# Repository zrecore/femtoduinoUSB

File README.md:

femtoduinoUSB
=============

Latest revision: FemtoduinoUSB r14.2

See the FemtoduinoUSB_r14 folder. It is a 4-layer EAGLE PCB design + schematic.

FemtoduinoUSB ATMEGA328P-MU Arduino Clone. Originally based on the Femtoduino by Fabio Varesano. Modified by Alex Albino to include FTDI USB to serial integration.

The femtoduino, and femtoduinoUSB is released under the following license: 

   CC-BY-SA 3.0 Unported
   http://creativecommons.org/licenses/by-sa/3.0/

The USB to UART circuit was completed in part thanks to Jim Paris' super-awesome MicroFTX schematics (http://jim.sh/ftx/), which are released under the following license:

   Creative Commons Attribution-ShareAlike 3.0 Unported License
   http://creativecommons.org/licenses/by-sa/3.0/
The pins on the latest revision are corrected to align perfectly with the original Femtoduino pin positions.

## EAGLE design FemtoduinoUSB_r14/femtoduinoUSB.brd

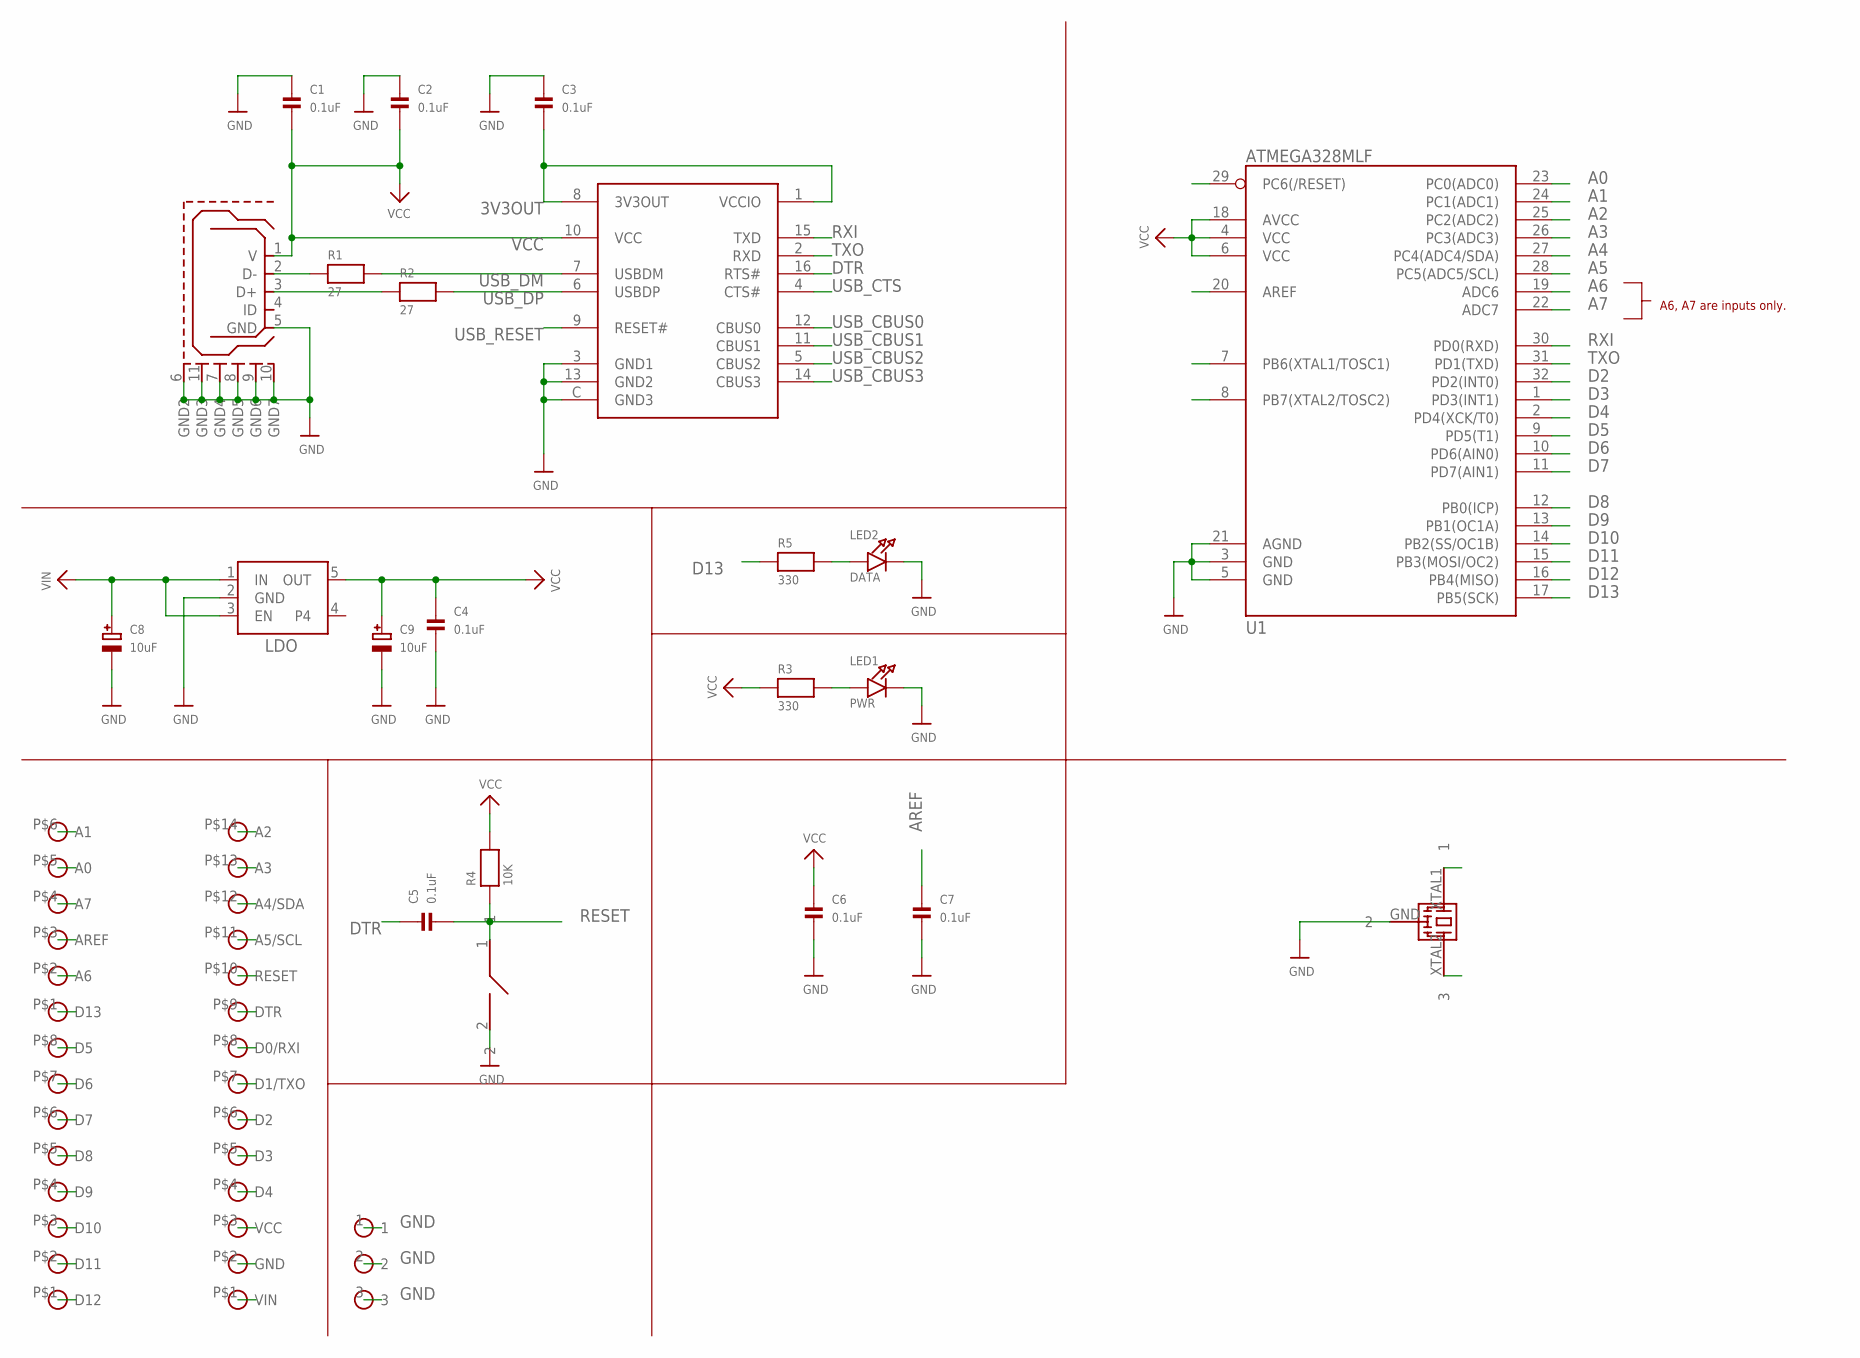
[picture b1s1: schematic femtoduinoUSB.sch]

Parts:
C1, C2, C3, C4, C5, C6, C7: 0.1uF; _0402MP
C8, C9: 10uF; EIA3216-18/A-R
LED1: PWR; CHIPLED_0603_NOOUTLINE
LED2: DATA; CHIPLED_0603_NOOUTLINE
R1, R2: 27; _0402MP
R3, R5: 330; _0402MP
R4: 10K; _0402
U1: ATMEGA328MLF; MLF32
U$1: FT230XQ
U$2: 05_PINHEAD_1X6; 05_PINHEAD_1X6_PACKAGE
U$3: 05_PINHEAD_1X8; 05_PINHEAD_1X8_PACKAGE
U$4: 05_PINHEAD_1X14; 05_PINHEAD_1X14_PACKAGE
U$6: USB_MICROB; USB_MICROB_PACKAGE
U$10: LDO_REGULATOR
U$17: SPST_SMD
U$22: CSTCE16MOV51-RO; CSTCE16M0V51-RO_PACKAGE
U$28: 05_PINHEAD_HEADER_1X3; 05_PINHEAD_1X3_HEAD_PACKAGE

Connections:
3V3OUT: C3.2, U$1.1 (VCCIO), U$1.8 (3V3OUT)
A0: U1.23 (PC0(ADC0)), U$2.P$5 (A0)
A1: U1.24 (PC1(ADC1)), U$2.P$6 (A1)
A2: U1.25 (PC2(ADC2)), U$4.P$14 (A2)
A3: U1.26 (PC3(ADC3)), U$4.P$13 (A3)
A4: U1.27 (PC4(ADC4/SDA)), U$4.P$12 (A4/SDA)
A5: U1.28 (PC5(ADC5/SCL)), U$4.P$11 (A5/SCL)
A6: U1.19 (ADC6), U$2.P$2 (A6)
A7: U1.22 (ADC7), U$2.P$4 (A7)
AREF: C7.1, U1.20 (AREF), U$2.P$3 (AREF)
D2: U1.32 (PD2(INT0)), U$4.P$6 (D2)
D3: U1.1 (PD3(INT1)), U$4.P$5 (D3)
D4: U1.2 (PD4(XCK/T0)), U$4.P$4 (D4)
D5: U1.9 (PD5(T1)), U$3.P$8 (D5)
D6: U1.10 (PD6(AIN0)), U$3.P$7 (D6)
D7: U1.11 (PD7(AIN1)), U$3.P$6 (D7)
D8: U1.12 (PB0(ICP)), U$3.P$5 (D8)
D9: U1.13 (PB1(OC1A)), U$3.P$4 (D9)
D10: U1.14 (PB2(SS/OC1B)), U$3.P$3 (D10)
D11: U1.15 (PB3(MOSI/OC2)), U$3.P$2 (D11)
D12: U1.16 (PB4(MISO)), U$3.P$1 (D12)
D13: R5.1, U1.17 (PB5(SCK)), U$2.P$1 (D13)
DTR: C5.1, U$1.16 (RTS#), U$4.P$9 (DTR)
GND: C1.1, C2.1, C3.1, C4.2, C6.2, C7.2, C8.-, C9.-, LED1.C, LED2.C, U1.3 (GND), U1.5 (GND), U1.21 (AGND), U$1.3 (GND1), U$1.13 (GND2), U$1.C (GND3), U$4.P$2 (GND), U$6.5 (GND), U$6.6 (GND2), U$6.7 (GND4), U$6.8 (GND5), U$6.9 (GND6), U$6.10 (GND7), U$6.11 (GND3), U$10.2 (GND), U$17.2, U$22.GND (2), U$28.1, U$28.2, U$28.3
unnamed: R1.1, U$6.2 (D-)
unnamed: R2.1, U$6.3 (D+)
unnamed: LED2.A, R5.2
unnamed: LED1.A, R3.2
RESET: C5.2, R4.1, U1.29 (PC6(/RESET)), U$4.P$10 (RESET), U$17.1
RXI: U1.30 (PD0(RXD)), U$1.15 (TXD), U$4.P$8 (D0/RXI)
TXO: U1.31 (PD1(TXD)), U$1.2 (RXD), U$4.P$7 (D1/TXO)
USB_CBUS0: U$1.12 (CBUS0)
USB_CBUS1: U$1.11 (CBUS1)
USB_CBUS2: U$1.5 (CBUS2)
USB_CBUS3: U$1.14 (CBUS3)
USB_CTS: U$1.4 (CTS#)
USB_DM: R1.2, U$1.7 (USBDM)
USB_DP: R2.2, U$1.6 (USBDP)
USB_RESET: U$1.9 (RESET#)
VCC: C1.2, C2.2, C4.1, C6.1, C9.+, R3.1, R4.2, U1.4 (VCC), U1.6 (VCC), U1.18 (AVCC), U$1.10 (VCC), U$4.P$3 (VCC), U$6.1 (V), U$10.5 (OUT)
VIN: C8.+, U$4.P$1 (VIN), U$10.1 (IN), U$10.3 (EN)
XTAL1: U1.7 (PB6(XTAL1/TOSC1)), U$22.XTAL1 (1)
XTAL2: U1.8 (PB7(XTAL2/TOSC2)), U$22.XTAL2 (3)

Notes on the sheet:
A6, A7 are inputs only.

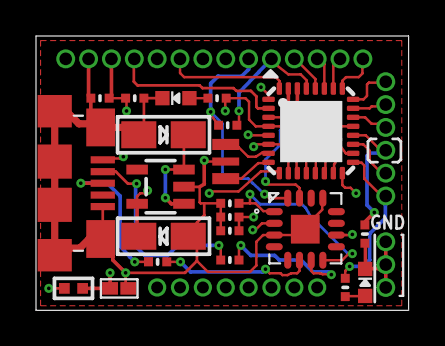
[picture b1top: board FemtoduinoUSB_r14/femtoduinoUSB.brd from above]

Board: 4 copper layers, 20.7 x 15.2 mm, 27 parts (1 on the bottom side), 37 nets.

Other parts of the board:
U$29: OSHW_6X70_NOTEXT

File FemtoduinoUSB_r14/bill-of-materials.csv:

"Qty";"Value";"Device/Manufacturer";"Package";"Parts";"Description"
"7";"0.1uF";"C1005X7R1A104K050BB";"0402";"C1, C2, C3, C4, C5, C6, C7";"Ceramic Capacitors"
"1";"DNP";;;"U$4";
"1";"DNP";;;"U$2";
"1";"DNP";;;"U$3";
"1";"DNP";;;"U$28";
"1";"10K";"CRCW040210K0JNEDHP";"_0402";"R4";"Resistors"
"2";"10uF";"TAJA106K016RNJ";"EIA3216-18/A-R";"C8, C9";"Tantalum Capacitors"
"2";"27";"CRCW040227R0FKED";"0402";"R1, R2";"Resistors"
"2";"330";"CRCW0402330RJNED";"0402";"R3, R5";"Resistors"
"1";"ATMEGA328MLF";"ATMEGA328P-MU";"MLF32";"U1";"Atmel 32-pin 8-bit micro, 32k flash."
"1";"16MHz";"CSTCE16M0V51-R0";"CSTCE16M0V51-R0_PACKAGE";"U$22";"This is the CSTCE16M0V51-R0 Murata resonator (CERALOCK) 16Mhz 0.5% Tolerance"
"1";"GREEN";"598-8070-102F";"0603";"LED2";"LED"
"1";"FT230XQ";"FT230XQ-R";"QFN-16";"U$1";
"1";"LDO_REGULATOR";"TPS76350DBVR";"SOT-23-5";"U$10";
"1";"RED";"598-8010-102F";"0603";"LED1";"LED"
"1";"DNP";;;"U$17";
"1";"USB_MICROB";"ZX62-B-5PA(11)";"USB_MICROB_PACKAGE";"U$6";"This is the hirose ZX62-B-5PA(11) MICRO-USB B Type female connection."

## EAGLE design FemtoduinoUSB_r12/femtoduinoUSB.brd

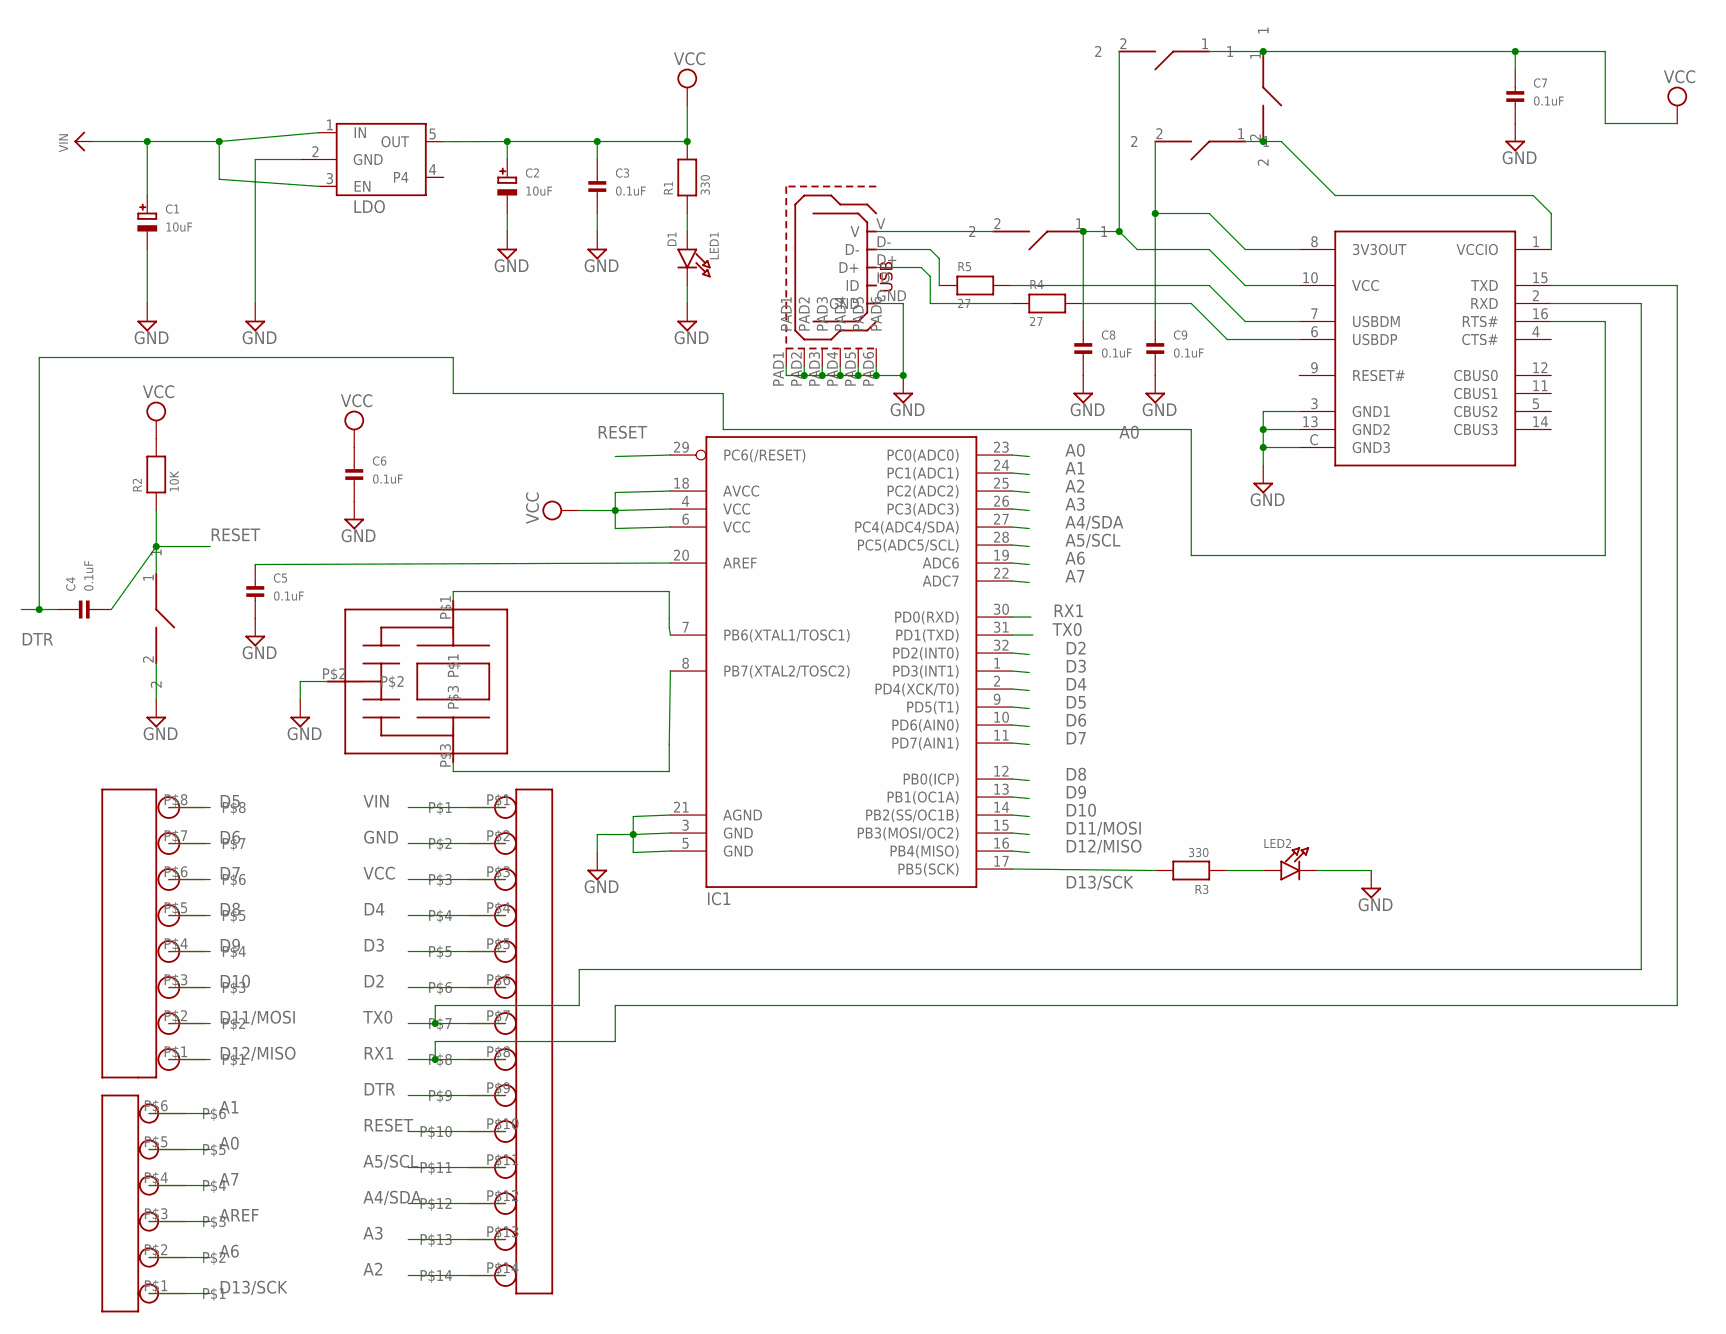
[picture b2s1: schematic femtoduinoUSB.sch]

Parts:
C1, C2: 10uF; EIA3528-21/B-W
C3, C4, C5, C6, C7, C8, C9: 0.1uF; 0402
IC1: ATMEGA168MLF; MLF32
LED1: D1; CHIPLED_0805
LED2: LED0805; CHIPLED_0805
R1, R3: 330; 0402
R2: 10K; 0402
R4, R5: 27; 0402
SJ1, SJ2, SJ3, SJ4: SPST_SMD
U1: MIC5205; LDO_REGULATOR
U$2: 05_PINHEAD_1X6; 05_PINHEAD_1X6_PACKAGE
U$3: 05_PINHEAD_1X8; 05_PINHEAD_1X8_PACKAGE
U$4: 05_PINHEAD_1X14; 05_PINHEAD_1X14_PACKAGE
U$5: CSTCE16MOV51-RO; CSTCE16M0V51-RO_PACKAGE
U$6: SPST_SMD
U$7: FT230XQ
USB1: USB_MICROB; USB_MICROB_PACKAGE

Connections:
3V3OUT: C9.1, SJ4.2, U$7.8 (3V3OUT)
A0: IC1.23 (PC0(ADC0)), U$2.P$5
A1: IC1.24 (PC1(ADC1)), U$2.P$6
A2: IC1.25 (PC2(ADC2)), U$4.P$14
A3: IC1.26 (PC3(ADC3)), U$4.P$13
A4/SDA: IC1.27 (PC4(ADC4/SDA)), U$4.P$12
A5/SCL: IC1.28 (PC5(ADC5/SCL)), U$4.P$11
A6: IC1.19 (ADC6), U$2.P$2
A7: IC1.22 (ADC7), U$2.P$4
AREF: C5.1, IC1.20 (AREF), U$2.P$3
D2: IC1.32 (PD2(INT0)), U$4.P$6
D3: IC1.1 (PD3(INT1)), U$4.P$5
D4: IC1.2 (PD4(XCK/T0)), U$4.P$4
D5: IC1.9 (PD5(T1)), U$3.P$8
D6: IC1.10 (PD6(AIN0)), U$3.P$7
D7: IC1.11 (PD7(AIN1)), U$3.P$6
D8: IC1.12 (PB0(ICP)), U$3.P$5
D9: IC1.13 (PB1(OC1A)), U$3.P$4
D10: IC1.14 (PB2(SS/OC1B)), U$3.P$3
D11/MOSI: IC1.15 (PB3(MOSI/OC2)), U$3.P$2
D12/MISO: IC1.16 (PB4(MISO)), U$3.P$1
D13/SCK: IC1.17 (PB5(SCK)), R3.2, U$2.P$1
D+: R4.2, U$7.6 (USBDP)
D-: R5.2, U$7.7 (USBDM)
DTR: C4.1, U$4.P$9, U$7.16 (RTS#)
GND: C1.-, C2.-, C3.2, C5.2, C6.2, C7.2, C8.2, C9.2, IC1.3 (GND), IC1.5 (GND), IC1.21 (AGND), LED1.C, LED2.C, U1.2 (GND), U$4.P$2, U$5.P$2, U$6.2, U$7.3 (GND1), U$7.13 (GND2), U$7.C (GND3), USB1.GND, USB1.PAD1, USB1.PAD2, USB1.PAD3, USB1.PAD4, USB1.PAD5, USB1.PAD6
unnamed: R4.1, USB1.D+
unnamed: R5.1, USB1.D-
unnamed: LED1.A, R1.1
unnamed: LED2.A, R3.1
PB6: IC1.7 (PB6(XTAL1/TOSC1)), U$5.P$1
PB7: IC1.8 (PB7(XTAL2/TOSC2)), U$5.P$3
RESET: C4.2, IC1.29 (PC6(/RESET)), R2.1, U$4.P$10, U$6.1
RX1: IC1.30 (PD0(RXD)), U$4.P$8, U$7.15 (TXD)
TX0: IC1.31 (PD1(TXD)), U$4.P$7, U$7.2 (RXD)
VCC: C2.+, C3.1, C6.1, C7.1, IC1.4 (VCC), IC1.6 (VCC), IC1.18 (AVCC), R1.2, R2.2, SJ1.2, SJ2.1, SJ3.1, U1.5 (OUT), U$4.P$3, USB1.V
VCCIO: SJ3.2, SJ4.1, U$7.1 (VCCIO)
VIN: C1.+, U1.1 (IN), U1.3 (EN), U$4.P$1
V_VCC: C8.1, SJ1.1, SJ2.2, U$7.10 (VCC)

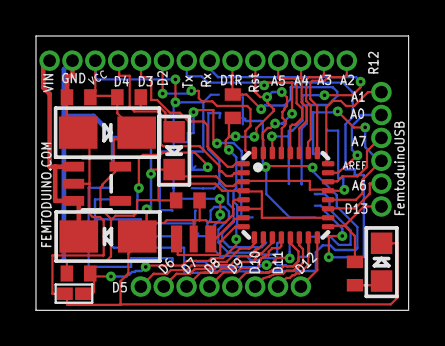
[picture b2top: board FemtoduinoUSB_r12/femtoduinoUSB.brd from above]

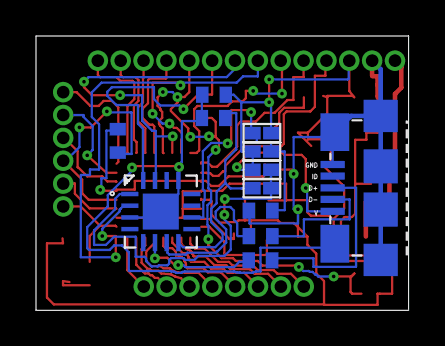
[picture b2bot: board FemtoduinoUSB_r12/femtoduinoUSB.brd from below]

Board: 2 copper layers, 20.7 x 15.2 mm, 29 parts (12 on the bottom side), 39 nets.

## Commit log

2012-12-25 Adding the femtoduinoUSB eagle cad files.
2013-01-14 Updates to the FemtoduinoUSB board
2013-02-26 Committing revision 9B of the FemtoduinoUSB. Minor corrections to the schematic, as the FTDI chip RESET# line was erroneously connected, instead of RST, to the ATMEGA DTR line. Additionally, a wire i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
2013-03-17 Adding revision 9C
2013-03-21 Committing changes to revision 9C, adding revision 10 with FTDI chip FT230 instead of FT231
2013-04-08 Committing revision 11
2013-04-16 FTDI chip footprint update
2013-04-26 Update README.md
    Adding in credit where credit is due! :-)
2013-05-24 Revision 12 - slightly enlarged through hole vias to make fabrication easier
2014-02-22 Adding revision 13 of the FemtoduinoUSB board
2015-01-15 Adding in FemtoduinoUSB revision 13 schematics and board file (EAGLE PCB)
2015-07-09 Releasing revision 14.2 of the Femtoduino USB (AVR powered, Arduino UNO compatible)
2015-07-09 Adding bill of materials for r14.2
2015-07-09 Updating README
2015-07-09 Minor update to Bill of Materials, adding parts list

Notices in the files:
parts and their libraries:
microbuilder: This work is placed in the public domain, and may be freely used for commercial and non-commercial work with the following conditions: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
SparkFun-DigitalIC: Licensing: CC v3.0 Share-Alike You are welcome to use this library for commercial purposes.
